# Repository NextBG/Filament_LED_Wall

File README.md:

# FilaWall

The extendable display wall

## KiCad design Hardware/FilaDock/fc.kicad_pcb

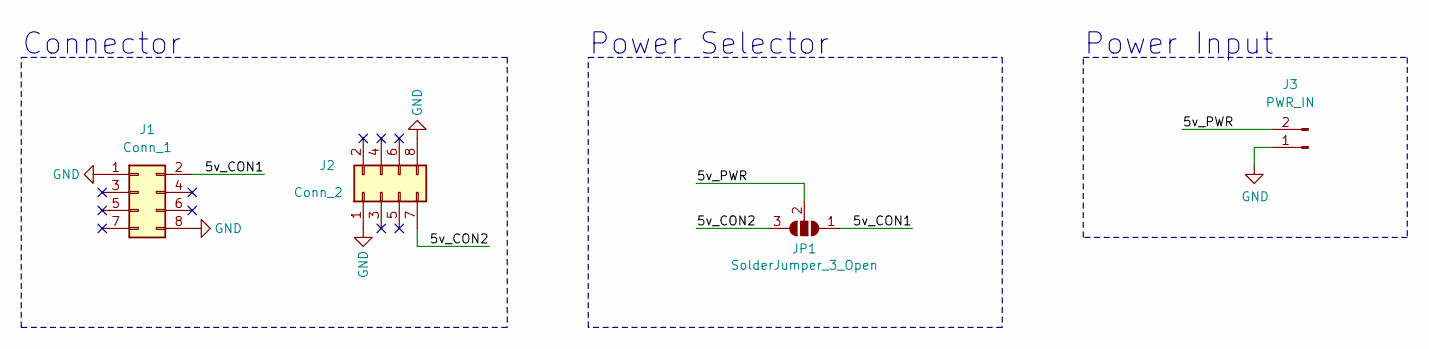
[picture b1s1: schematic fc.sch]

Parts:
J1: Conn_1; PinSocket_2x04_P2.54mm_Vertical
J2: Conn_2; PinSocket_2x04_P2.54mm_Vertical
J3: PWR_IN; PinHeader_1x02_P2.54mm_Horizontal
JP1: SolderJumper_3_Open; SolderJumper-3_P1.3mm_Open_RoundedPad1.0x1.5mm

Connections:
/5v_CON1: J1.2, JP1.1 (A)
/5v_CON2: J2.7, JP1.3 (B)
/5v_PWR: J3.2, JP1.2 (C)
GND: J1.1, J1.8, J2.1, J2.8, J3.1

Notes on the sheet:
Connector
Power Selector
Power Input

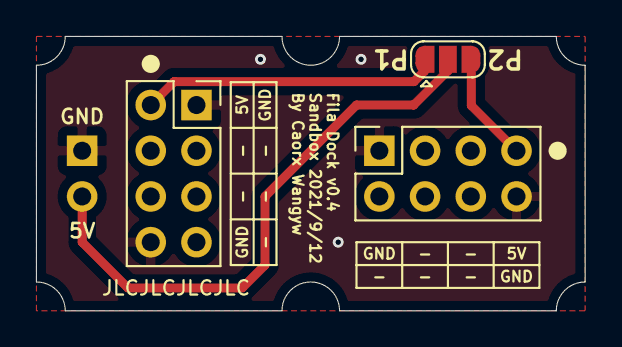
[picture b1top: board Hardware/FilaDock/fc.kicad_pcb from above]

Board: 2 copper layers, 30.5 x 15.2 mm, 4 parts (1 on the bottom side), 4 nets.

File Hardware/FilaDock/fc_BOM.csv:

Comment,Description,Designator,Footprint,LibRef,Pins,Quantity,±àºÅ
SolderJumper_3_Open,Desc,"JP1,",SolderJumper-3_P1.3mm_Open_RoundedPad1.0x1.5mm,LibRef,3,1
Through Hole Items 
Conn_1,Desc,"J1,",PinSocket_2x04_P2.54mm_Vertical,LibRef,8,1
Conn_2,Desc,"J2,",PinSocket_2x04_P2.54mm_Vertical,LibRef,8,1
PWR_IN,Desc,"J3,",PinHeader_1x02_P2.54mm_Horizontal,LibRef,2,1

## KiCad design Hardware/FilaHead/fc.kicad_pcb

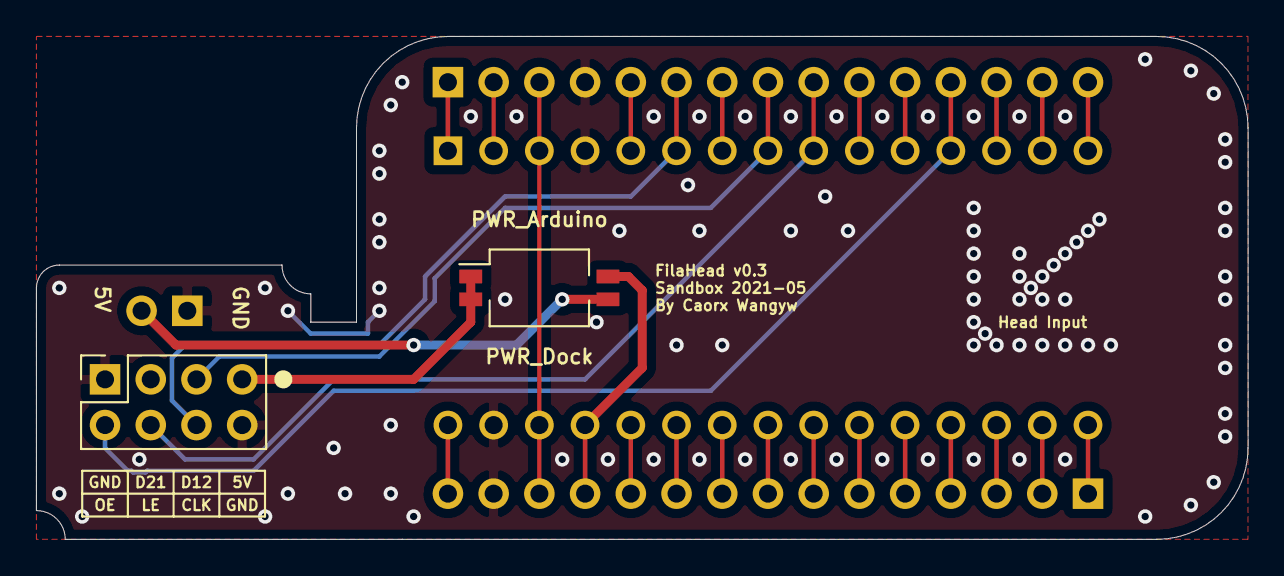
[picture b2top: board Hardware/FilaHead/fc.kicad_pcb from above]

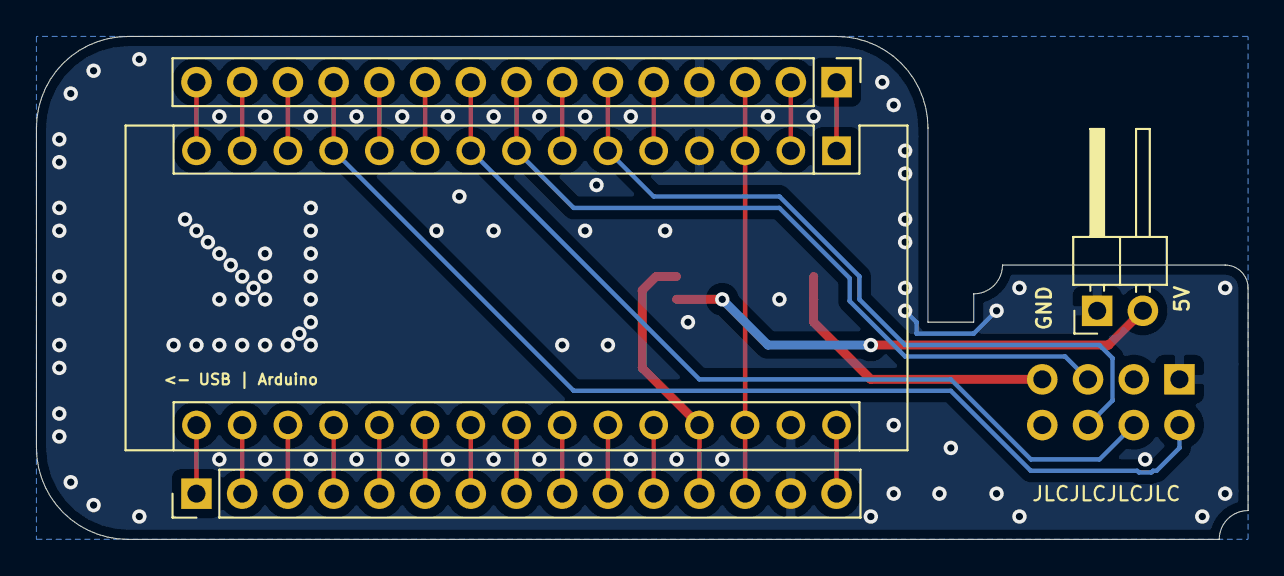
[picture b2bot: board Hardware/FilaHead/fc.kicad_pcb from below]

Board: 2 copper layers, 67.3 x 27.9 mm, 6 parts (4 on the bottom side), 30 nets.

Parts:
A1: Arduino_Nano_v2.x; Arduino_Nano
J1, J4: Conn_01x15_Female; PinHeader_1x15_P2.54mm_Vertical
J2: Conn_2; PinSocket_2x04_P2.54mm_Vertical
J3: PWR_IN; PinHeader_1x02_P2.54mm_Horizontal
SW1: PowerSel; SW_DIP_SPSTx02_Slide_KingTek_DSHP02TS_W7.62mm_P1.27mm

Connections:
/5v_CON2: J2.7, SW1.1, SW1.2
/5v_PWR: J3.2, SW1.3
A0: A1.19, J1.4
A1: A1.20, J1.5
A2: A1.21, J1.6
A3: A1.22, J1.7
A4: A1.23, J1.8
A5: A1.24, J1.9
A6: A1.25, J1.10
A7: A1.26, J1.11
A_3V3: A1.17, J1.2
A_5V: A1.27, J1.12, SW1.4
A_REF: A1.18, J1.3
A_RST: A1.3, A1.28, J1.13, J4.3
A_VIN: A1.30, J1.15
CLK: A1.6, J2.6, J4.6
D2: A1.5, J4.5
D4: A1.7, J4.7
D7: A1.10, J4.10
D8: A1.11, J4.11
D12: A1.15, J4.15
D13: A1.16, J1.1
GND: A1.4, A1.29, J1.14, J2.1, J2.8, J3.1, J4.4
LE: A1.9, J2.4, J4.9
OE: A1.12, J2.2, J4.12
PWM5: A1.8, J2.5, J4.8
PWM10: A1.13, J4.13
PWM11: A1.14, J4.14
RX0: A1.2, J4.2
TX1: A1.1, J4.1

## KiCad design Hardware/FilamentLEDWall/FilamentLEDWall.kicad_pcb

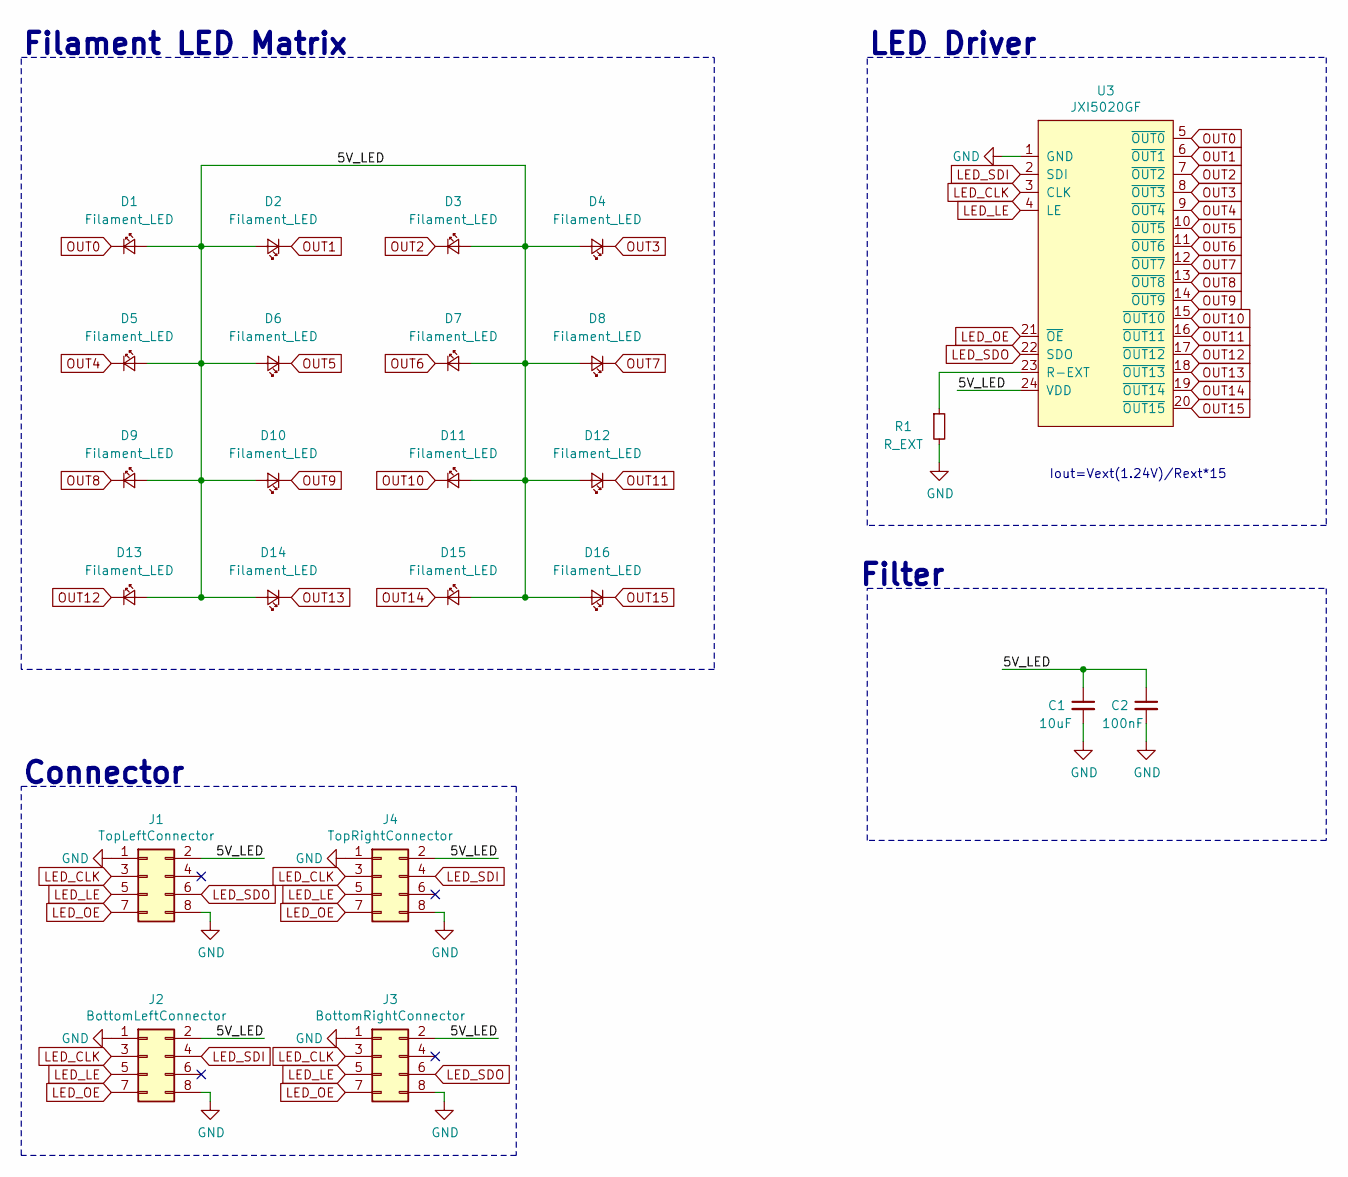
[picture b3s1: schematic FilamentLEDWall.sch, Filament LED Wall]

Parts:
C1: 10uF; C_0603_1608Metric_Pad1.05x0.95mm_HandSolder
C2: 100nF; C_0603_1608Metric_Pad1.05x0.95mm_HandSolder
D1, D2, D3, D4, D5, D6, D7, D8, D9, D10, D11, D12, D13, D14, D15, D16: Filament_LED; FilamentLED_30mm
J1: TopLeftConnector; PinHeader_2x04_P2.54mm_Vertical_SMD
J2: BottomLeftConnector; PinHeader_2x04_P2.54mm_Vertical_SMD
J3: BottomRightConnector; PinHeader_2x04_P2.54mm_Vertical_SMD
J4: TopRightConnector; PinHeader_2x04_P2.54mm_Vertical_SMD
R1: R_EXT; R_0603_1608Metric_Pad1.05x0.95mm_HandSolder
U3: JXI5020GF; Allegro_QSOP-24_3.9x8.7mm_P0.635mm

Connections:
/5V_LED: C1.1, C2.1, D1.2 (A), D2.2 (A), D3.2 (A), D4.2 (A), D5.2 (A), D6.2 (A), D7.2 (A), D8.2 (A), D9.2 (A), D10.2 (A), D11.2 (A), D12.2 (A), D13.2 (A), D14.2 (A), D15.2 (A), D16.2 (A), J1.2, J2.2, J3.2, J4.2, U3.24 (VDD)
GND: C1.2, C2.2, J1.1, J1.8, J2.1, J2.8, J3.1, J3.8, J4.1, J4.8, R1.2, U3.1 (GND)
LED_CLK: J1.3, J2.3, J3.3, J4.3, U3.3 (CLK)
LED_LE: J1.5, J2.5, J3.5, J4.5, U3.4 (LE)
LED_OE: J1.7, J2.7, J3.7, J4.7, U3.21 (~OE)
LED_SDI: J2.4, J4.4, U3.2 (SDI)
LED_SDO: J1.6, J3.6, U3.22 (SDO)
unnamed: R1.1, U3.23 (R-EXT)
OUT0: D1.1 (K), U3.5 (~OUT0)
OUT1: D2.1 (K), U3.6 (~OUT1)
OUT2: D3.1 (K), U3.7 (~OUT2)
OUT3: D4.1 (K), U3.8 (~OUT3)
OUT4: D5.1 (K), U3.9 (~OUT4)
OUT5: D6.1 (K), U3.10 (~OUT5)
OUT6: D7.1 (K), U3.11 (~OUT6)
OUT7: D8.1 (K), U3.12 (~OUT7)
OUT8: D9.1 (K), U3.13 (~OUT8)
OUT9: D10.1 (K), U3.14 (~OUT9)
OUT10: D11.1 (K), U3.15 (~OUT10)
OUT11: D12.1 (K), U3.16 (~OUT11)
OUT12: D13.1 (K), U3.17 (~OUT12)
OUT13: D14.1 (K), U3.18 (~OUT13)
OUT14: D15.1 (K), U3.19 (~OUT14)
OUT15: D16.1 (K), U3.20 (~OUT15)

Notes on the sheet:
Iout=Vext(1.24V)/Rext*15
LED Driver
Filament LED Matrix
Connector
Filter

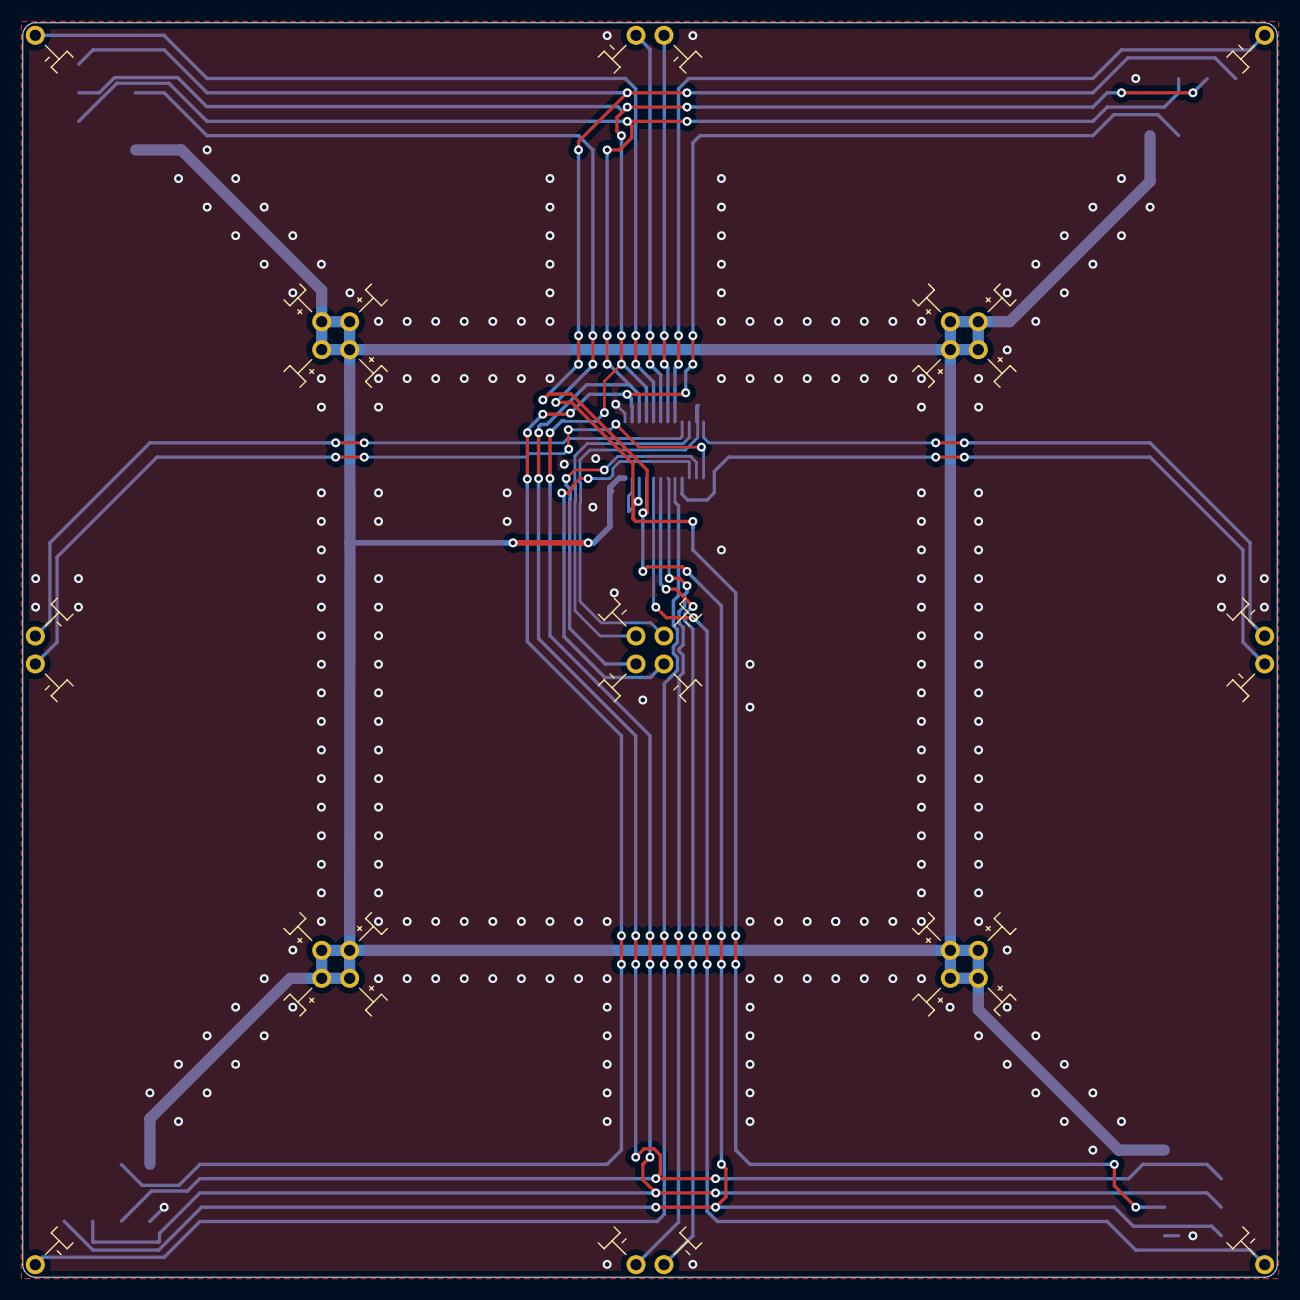
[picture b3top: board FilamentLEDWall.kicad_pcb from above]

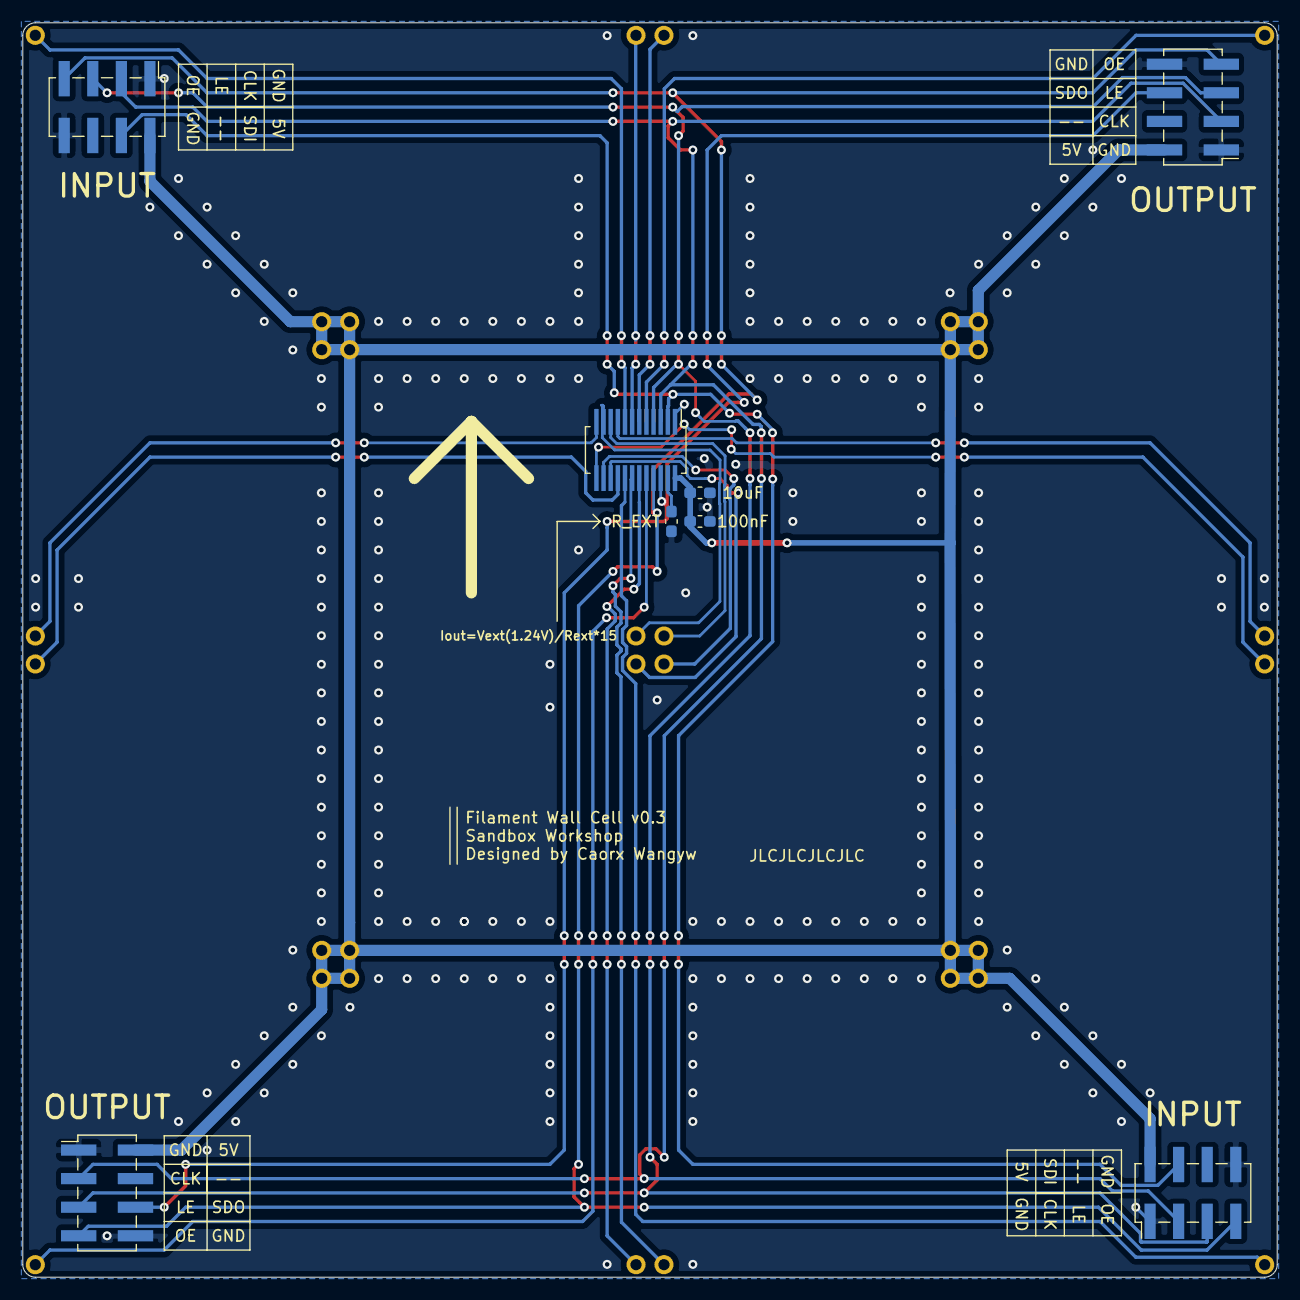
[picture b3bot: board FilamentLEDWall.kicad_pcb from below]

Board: 2 copper layers, 111.5 x 111.5 mm, 24 parts (8 on the bottom side), 24 nets.

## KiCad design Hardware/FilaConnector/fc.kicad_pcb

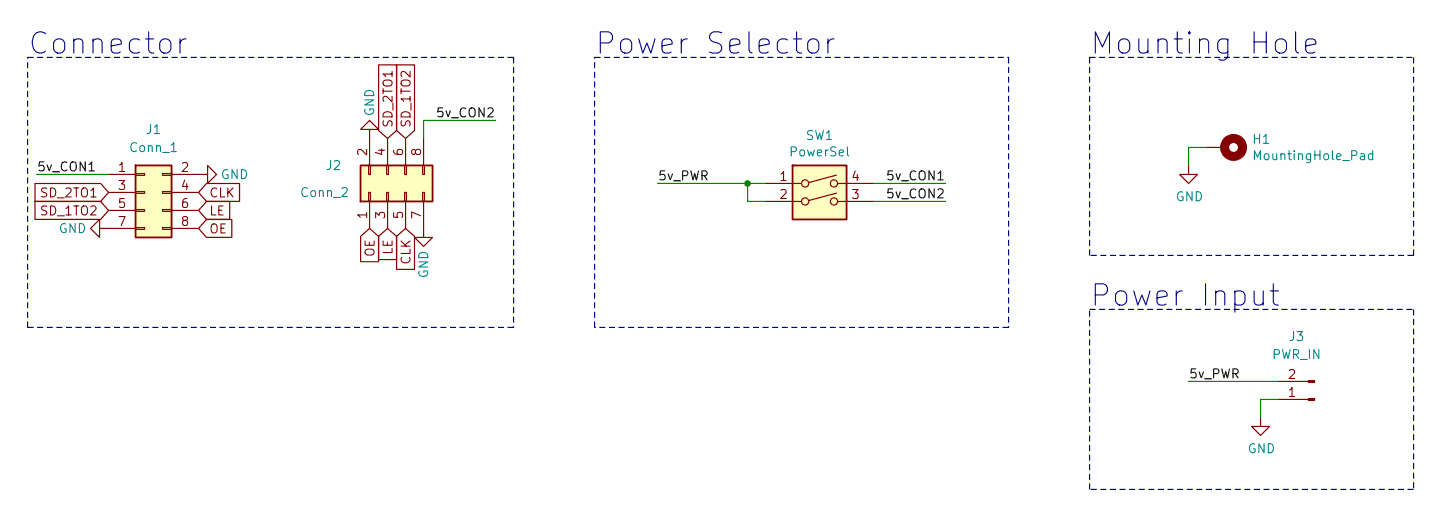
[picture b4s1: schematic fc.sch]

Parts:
H1: MountingHole_Pad; MountingHole_2.2mm_M2_Pad
J1: Conn_1; PinHeader_2x04_P2.54mm_Vertical
J2: Conn_2; PinHeader_2x04_P2.54mm_Vertical
J3: PWR_IN; PinHeader_1x02_P2.54mm_Horizontal
SW1: PowerSel; SW_DIP_SPSTx02_Slide_KingTek_DSHP02TS_W7.62mm_P1.27mm

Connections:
/5v_CON1: J1.1, SW1.4
/5v_CON2: J2.8, SW1.3
/5v_PWR: J3.2, SW1.1, SW1.2
CLK: J1.4, J2.5
GND: H1.1, J1.2, J1.7, J2.2, J2.7, J3.1
LE: J1.6, J2.3
OE: J1.8, J2.1
SD_1TO2: J1.5, J2.6
SD_2TO1: J1.3, J2.4

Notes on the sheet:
Connector
Power Selector
Mounting Hole
Power Input

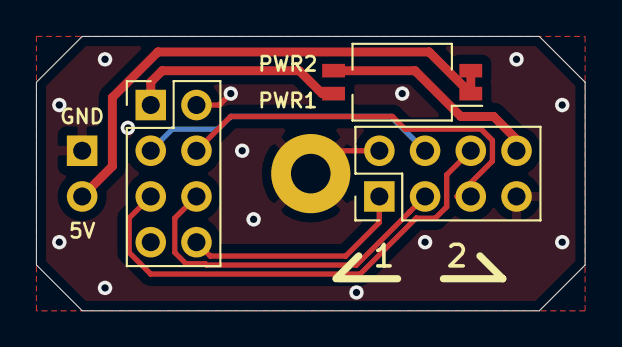
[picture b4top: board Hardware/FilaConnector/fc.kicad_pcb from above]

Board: 2 copper layers, 30.5 x 15.2 mm, 5 parts (1 on the bottom side), 9 nets.

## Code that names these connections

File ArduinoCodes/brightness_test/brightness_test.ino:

#define LED_OE  9
#define LED_LE  6
#define LED_CLK 3
#define LED_SDI 5

#define DELAY_TIME 1

void setup() {
  Serial.begin(115200);
  
  pinMode(LED_OE,OUTPUT);
  pinMode(LED_LE,OUTPUT);
  pinMode(LED_CLK,OUTPUT);
  pinMode(LED_SDI,OUTPUT);

  digitalWrite(LED_OE,HIGH);
  digitalWrite(LED_LE,LOW);
  digitalWrite(LED_SDI,HIGH);
  digitalWrite(LED_CLK,LOW);
  Serial.println("Init done!");

  digitalWrite(LED_OE,LOW);
  DisplayLED(0x0000);
}

void loop() 
{
  TestLED();
}

void TestLED()
{
    // PWM adjust the brightness    
    DisplayLED(0xFFFF);
    delayMicroseconds(500);
    DisplayLED(0x0000);
    delayMicroseconds(500);
}

void DisplayLED(unsigned long data)
{
  int i = 0;
  for(i=0;i<16;i++)
  {
    digitalWrite(LED_SDI,data>>i & 0x01);
    digitalWrite(LED_CLK,HIGH);
    digitalWrite(LED_CLK,LOW);
  }
  digitalWrite(LED_LE,HIGH);
  digitalWrite(LED_LE,LOW);
}

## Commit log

2021-03-04 backups
2021-03-04 backuped iOS project
2021-03-04 backuped iOS icons
2021-03-04 updated iOS project
2021-03-09 added Docs/API
2021-03-12 init ios project
2021-03-12 updated PCB
2021-03-12 new branch added
2021-04-01 updated ios proj
2021-04-01 updated circuit
2021-04-02 backup
2021-04-02 init connector
2021-04-02 Updated light PCB v0.1
2021-04-04 Updated LED Board to v0.2
2021-04-04 created Placeholder & Head[WIP]
2021-04-05 updated arduino nano connector
2021-04-05 updated hardware and RPi codes
2021-04-05 Updated Fila Head
2021-04-05 updated and generated Header connector
2021-04-07 updated wall cell and connector
2021-04-07 updated packages
2021-04-10 added FilaWallCore - PIO project
2021-04-15 merged all
2021-04-25 Updated 3dprinted frame
2021-04-25 Updated FilaDock component
2021-05-02 updated FilaHead v0.3
2021-05-04 upload latest head PCB
2021-05-04 optimized pcb
2021-05-04 rounded corners
2021-05-04 generated production files
2021-05-05 reformatted arduino
2021-05-05 added new arduino logic
    [!] Warning: this is not based on the latest version. Should use the one in SDB computer to OVERWRITE this.
2021-09-20 re-arranged project files
2021-09-20 added class for FilaWall
2021-09-20 added video capture and writer
